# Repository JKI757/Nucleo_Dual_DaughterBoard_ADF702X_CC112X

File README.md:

## About the Project

- This project is a simple PCB for an STM32 Nucleo-64 Hat that provides an interface between the hat and an Analog Devices [ADF-702X](https://www.analog.com/en/design-center/evaluation-hardware-and-software/evaluation-boards-kits/eval-adf7021-n.html) development board and a Texas Instruments [CC112X EMK](https://www.ti.com/tool/CC1120EMK-420-470) development board.

The project includes both the Kicad schematic and PCB files, and the STM project for the Nucleo-64 L452RE.

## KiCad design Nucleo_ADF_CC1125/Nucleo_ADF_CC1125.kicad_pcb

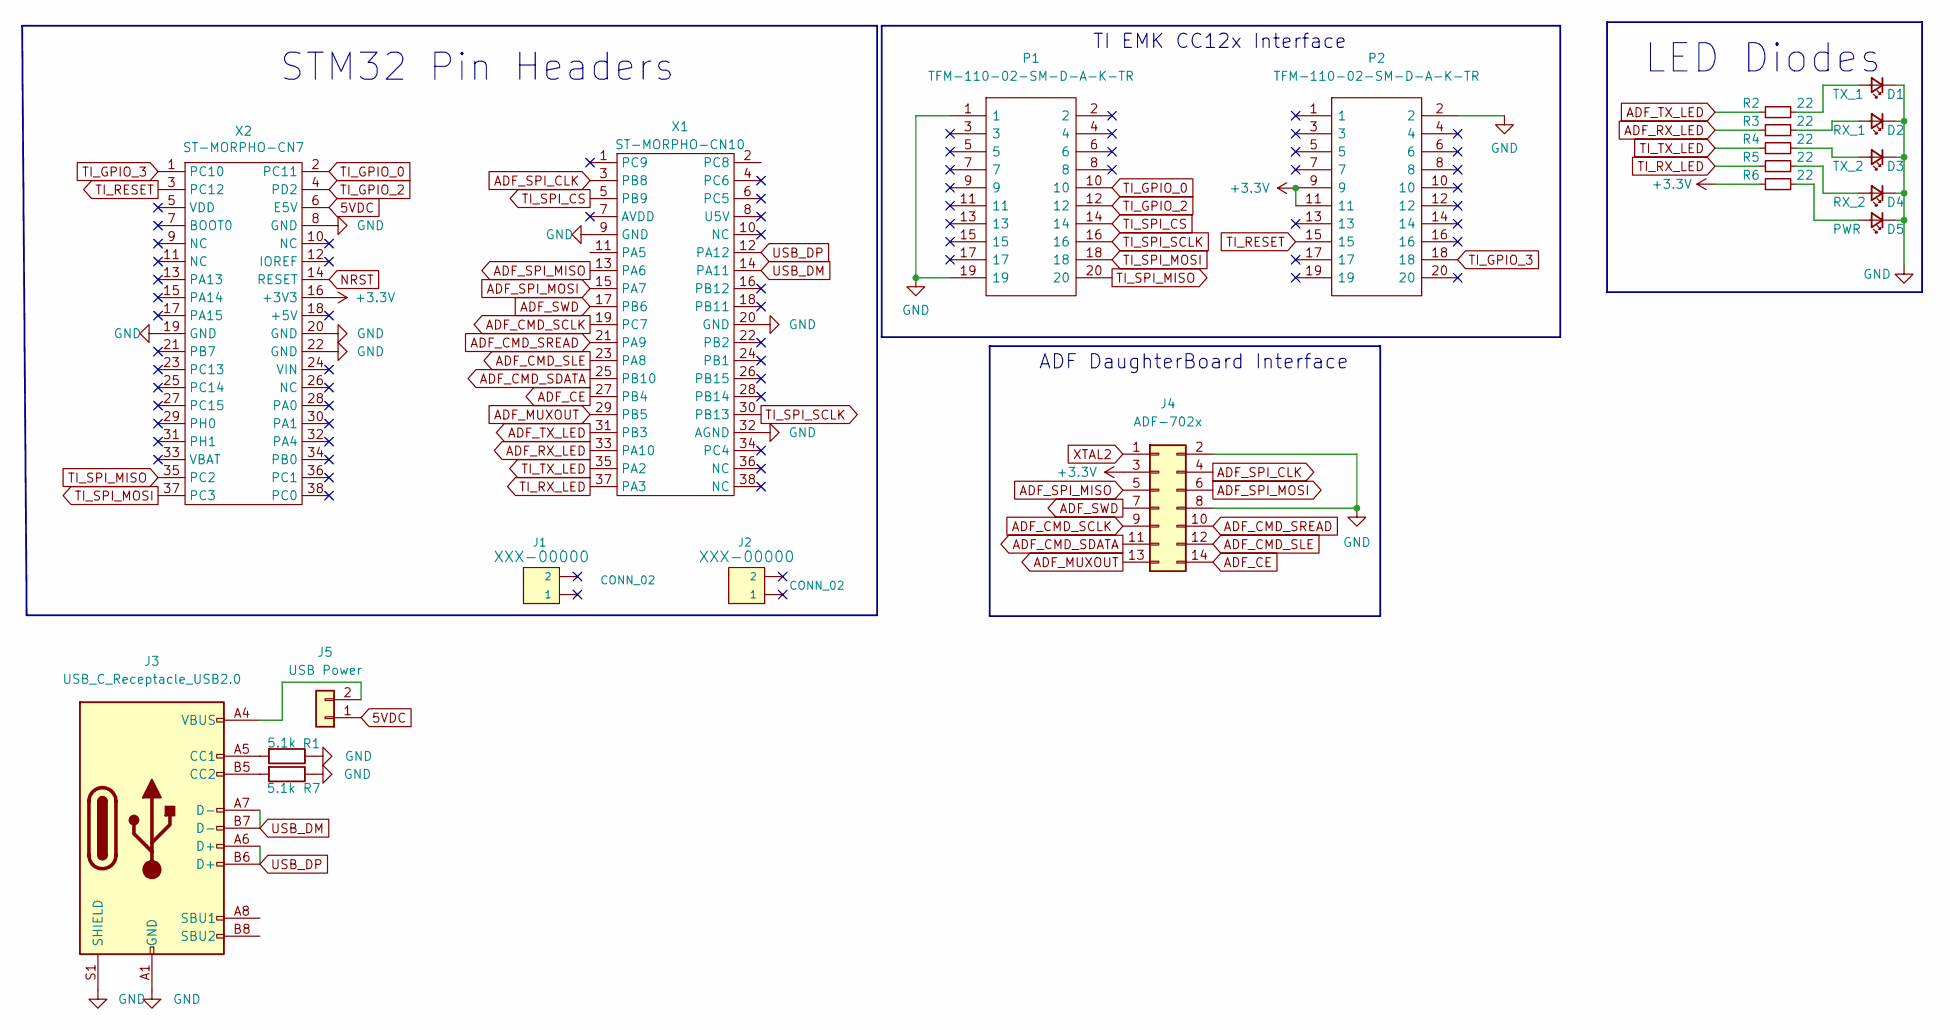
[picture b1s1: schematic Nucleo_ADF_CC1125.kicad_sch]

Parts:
D1: TX_1; LED_0402_1005Metric
D2: RX_1; LED_0402_1005Metric
D3: TX_2; LED_0402_1005Metric
D4: RX_2; LED_0402_1005Metric
D5: PWR; LED_0402_1005Metric
J1, J2: CONN_02; PinSocket_1x02_P2.54mm_Vertical
J3: USB_C_Receptacle_USB2.0; USB_C_Receptacle_JAE_DX07S016JA1R1500
J4: ADF-702x; PinHeader_2x07_P2.54mm_Vertical
J5: USB Power; PinHeader_1x02_P2.54mm_Vertical
P1, P2: TFM-110-02-SM-D-A-K-TR; TFM-110-02-XXX-D-A-Y-TR; Mouser Part Number 200-TFM11002SMDAKTR
R1, R7: 5.1k; R_0402_1005Metric
R2, R3, R4, R5, R6: 22; R_0402_1005Metric
X1: ST-MORPHO-CN10; PinSocket_2x19_P2.54mm_Vertical
X2: ST-MORPHO-CN7; PinSocket_2x19_P2.54mm_Vertical

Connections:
5VDC: J5.1, X2.6 (E5V)
+3V3: J4.3, P2.9, P2.11, R6.1, X2.16 (+3V3)
ADF_CE: J4.14, X1.27 (PB4)
ADF_CMD_SCLK: J4.9, X1.19 (PC7)
ADF_CMD_SDATA: J4.11, X1.25 (PB10)
ADF_CMD_SLE: J4.12, X1.23 (PA8)
ADF_CMD_SREAD: J4.10, X1.21 (PA9)
ADF_MUXOUT: J4.13, X1.29 (PB5)
ADF_RX_LED: R3.1, X1.33 (PA10)
ADF_SPI_CLK: J4.4, X1.3 (PB8)
ADF_SPI_MISO: J4.5, X1.13 (PA6)
ADF_SPI_MOSI: J4.6, X1.15 (PA7)
ADF_SWD: J4.7, X1.17 (PB6)
ADF_TX_LED: R2.1, X1.31 (PB3)
GND: D1.1 (K), D2.1 (K), D3.1 (K), D4.1 (K), D5.1 (K), J3.A1 (GND), J3.A12 (GND), J3.B1 (GND), J3.B12 (GND), J3.S1 (SHIELD), J4.2, J4.8, P1.1, P1.19, P2.2, R1.1, R7.1, X1.9 (GND), X1.20 (GND), X1.32 (AGND), X2.8 (GND), X2.19 (GND), X2.20 (GND), X2.22 (GND)
NRST: X2.14 (RESET)
unnamed: D1.2 (A), R2.2
unnamed: D2.2 (A), R3.2
unnamed: D3.2 (A), R4.2
unnamed: D4.2 (A), R5.2
unnamed: D5.2 (A), R6.2
unnamed: J3.A4 (VBUS), J3.A9 (VBUS), J3.B4 (VBUS), J3.B9 (VBUS), J5.2
unnamed: J3.A5 (CC1), R1.2
unnamed: J3.B5 (CC2), R7.2
TI_GPIO_0: P1.10, X2.2 (PC11)
TI_GPIO_2: P1.12, X2.4 (PD2)
TI_GPIO_3: P2.18, X2.1 (PC10)
TI_RESET: P2.15, X2.3 (PC12)
TI_RX_LED: R5.1, X1.37 (PA3)
TI_SPI_CS: P1.14, X1.5 (PB9)
TI_SPI_MISO: P1.20, X2.35 (PC2)
TI_SPI_MOSI: P1.18, X2.37 (PC3)
TI_SPI_SCLK: P1.16, X1.30 (PB13)
TI_TX_LED: R4.1, X1.35 (PA2)
USB_DM: J3.A7 (D-), J3.B7 (D-), X1.14 (PA11)
USB_DP: J3.A6 (D+), J3.B6 (D+), X1.12 (PA12)
XTAL2: J4.1

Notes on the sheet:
TI EMK CC12x Interface
STM32 Pin Headers
LED Diodes
ADF DaughterBoard Interface

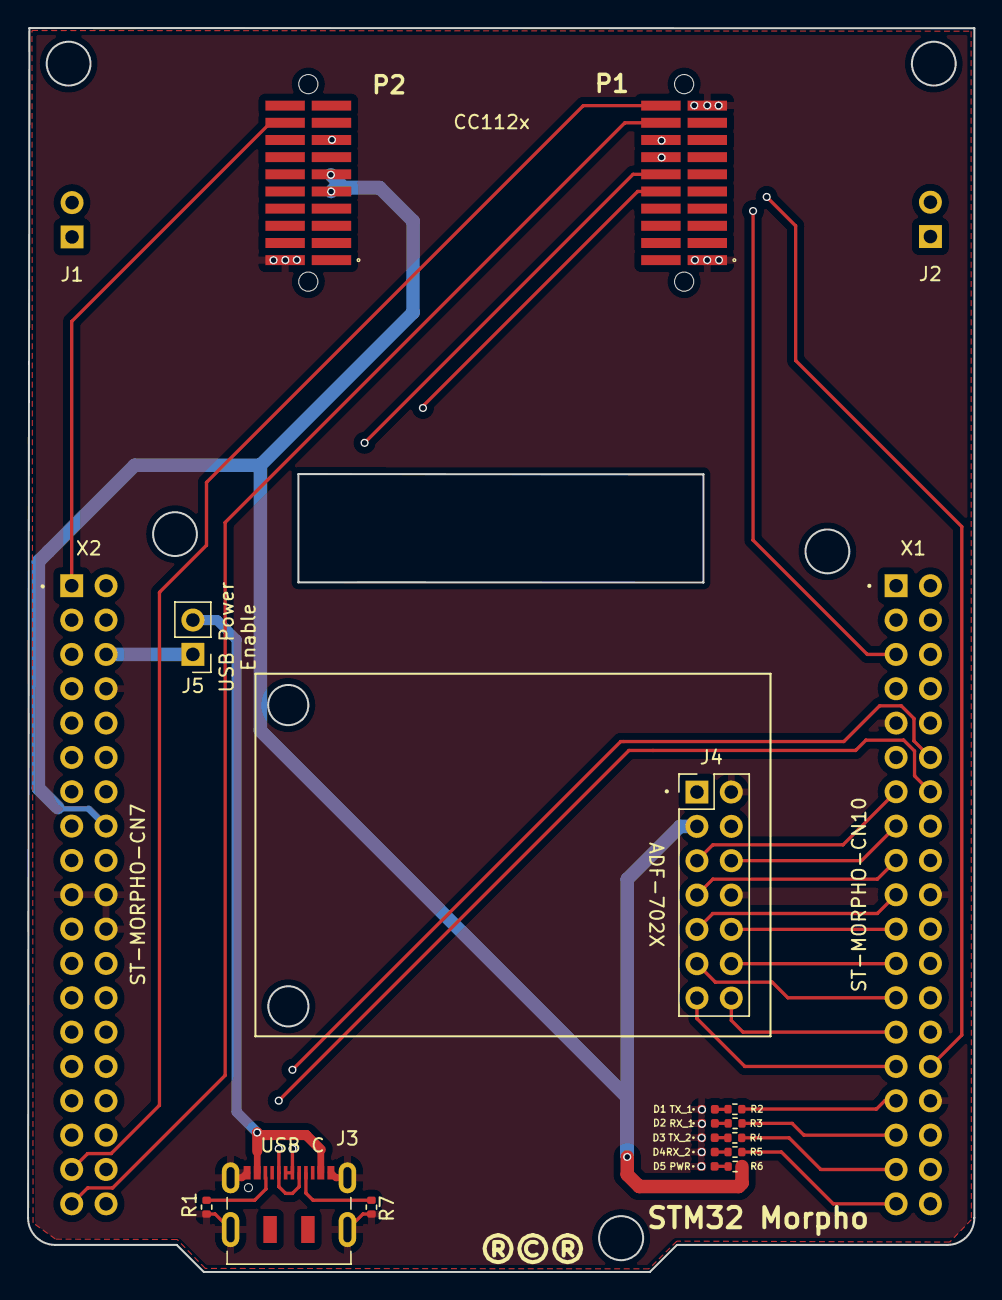
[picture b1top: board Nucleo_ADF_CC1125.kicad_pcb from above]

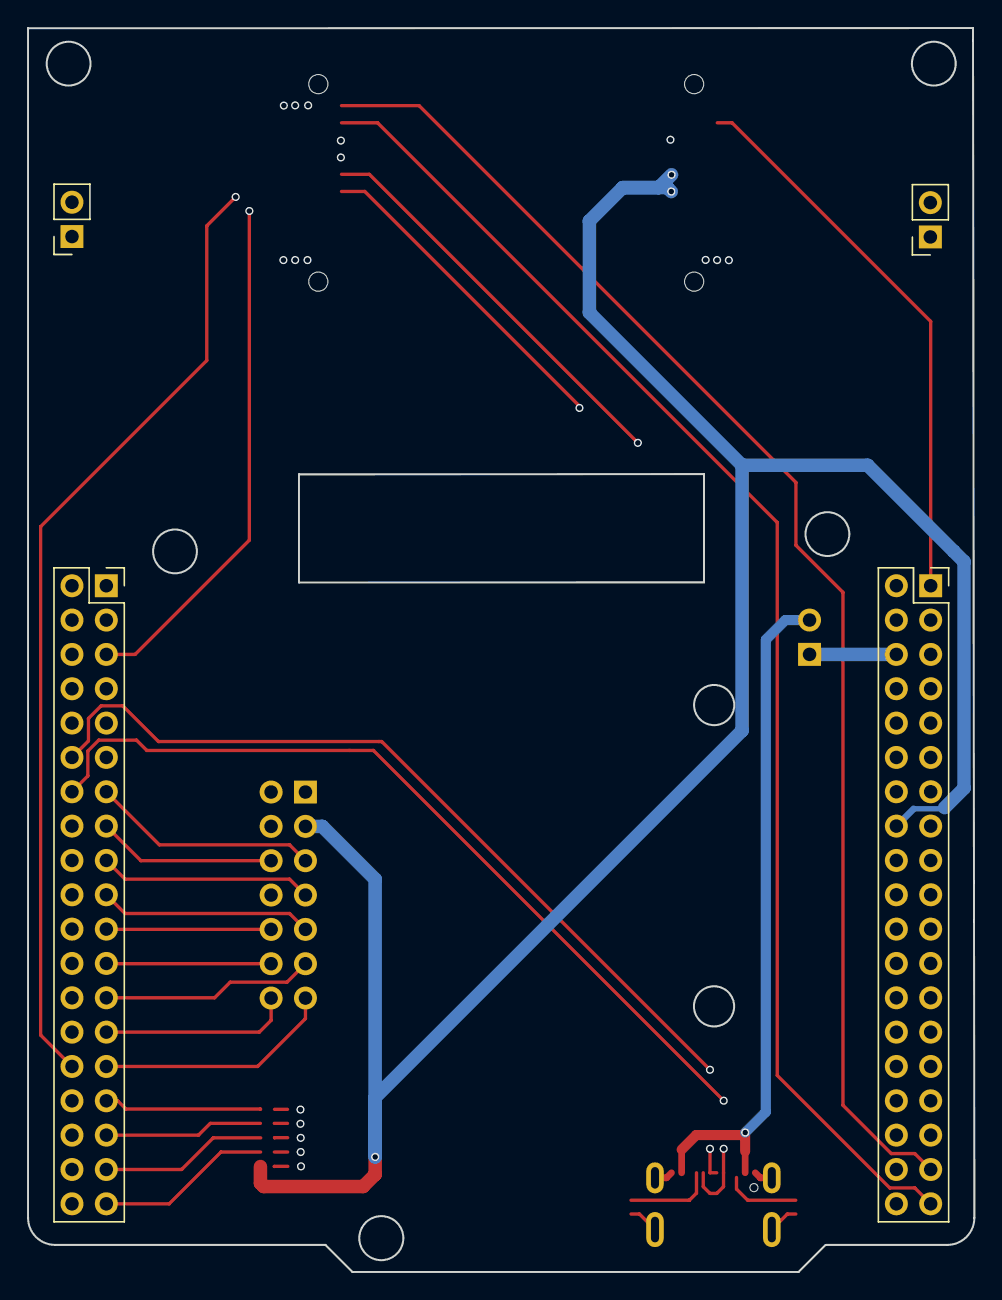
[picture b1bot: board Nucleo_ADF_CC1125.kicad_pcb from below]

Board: 4 copper layers, 70.0 x 92.0 mm, 21 parts (4 on the bottom side), 35 nets.

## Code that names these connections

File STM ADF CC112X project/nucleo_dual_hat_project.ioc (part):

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Mcu.Name=STM32L452R(C-E)Tx
Mcu.Package=LQFP64
Mcu.UserName=STM32L452RETx
PA10.GPIOParameters=GPIO_Label
PA10.GPIO_Label=ADF_RX_LED
PA10.Signal=GPIO_Output
PA11.Mode=Device
PA11.Signal=USB_DM
PA12.Mode=Device
PA12.Signal=USB_DP
PA13\ (JTMS/SWDIO).GPIOParameters=GPIO_Label
PA13\ (JTMS/SWDIO).GPIO_Label=TMS
PA13\ (JTMS/SWDIO).Mode=Serial_Wire
PA13\ (JTMS/SWDIO).Signal=SYS_JTMS-SWDIO
PA14\ (JTCK/SWCLK).GPIOParameters=GPIO_Label
PA14\ (JTCK/SWCLK).GPIO_Label=TCK
PA14\ (JTCK/SWCLK).Mode=Serial_Wire
PA14\ (JTCK/SWCLK).Signal=SYS_JTCK-SWCLK
PA2.GPIOParameters=GPIO_Label
PA2.GPIO_Label=TI_TX_LED
PA2.Signal=GPIO_Output
PA3.GPIOParameters=GPIO_Label
PA3.GPIO_Label=TI_RX_LED
PA3.Signal=GPIO_Output
PA5.GPIOParameters=GPIO_Speed,GPIO_PuPd,GPIO_Label,GPIO_ModeDefaultOutputPP
PA5.GPIO_Label=LD4 [green Led]
PA5.GPIO_ModeDefaultOutputPP=GPIO_MODE_OUTPUT_PP
PA5.GPIO_PuPd=GPIO_NOPULL
PA5.GPIO_Speed=GPIO_SPEED_FREQ_LOW
PA5.Signal=GPIO_Output
PA6.GPIOParameters=GPIO_Label
PA6.GPIO_Label=ADF_SPI_MISO
PA6.Signal=GPIO_Output
PA7.GPIOParameters=GPIO_Label
PA7.GPIO_Label=ADF_SPI_MOSI
PA7.Signal=GPIO_Input
PA8.GPIOParameters=GPIO_Label
PA8.GPIO_Label=ADF_CMD_SLE
PA8.Signal=GPIO_Output
PA9.GPIOParameters=GPIO_Label
PA9.GPIO_Label=ADF_CMD_SREAD
PA9.Signal=GPIO_Input
PB10.GPIOParameters=GPIO_Label
PB10.GPIO_Label=ADF_CMD_SDATA
PB10.Signal=GPIO_Output
PB13.Mode=Full_Duplex_Master
PB13.Signal=SPI2_SCK
PB3\ (JTDO/TRACESWO).GPIOParameters=GPIO_Label
PB3\ (JTDO/TRACESWO).GPIO_Label=ADF_TX_LED
PB3\ (JTDO/TRACESWO).Signal=GPIO_Output
PB4\ (NJTRST).GPIOParameters=GPIO_Label
PB4\ (NJTRST).GPIO_Label=ADF_CE
PB4\ (NJTRST).Signal=GPIO_Output
PB5.GPIOParameters=GPIO_Label
PB5.GPIO_Label=ADF_MUXOUT
PB5.Signal=GPIO_Input
PB6.GPIOParameters=GPIO_Label
PB6.GPIO_Label=ADF_SWD
PB6.Signal=GPXTI6
PB8.GPIOParameters=GPIO_Label
PB8.GPIO_Label=ADF_SPI_CLK
PB8.Signal=GPXTI8
PB9.Mode=NSS_Signal_Hard_Output
PB9.Signal=SPI2_NSS
PC10.GPIOParameters=GPIO_Label
PC10.GPIO_Label=TI_GPIO_3
PC10.Signal=GPXTI10
PC11.GPIOParameters=GPIO_Label
PC11.GPIO_Label=TI_GPIO_0
PC11.Signal=GPXTI11
PC12.GPIOParameters=GPIO_Label
PC12.GPIO_Label=TI_RESET
PC12.Signal=GPIO_Output
PC13.GPIOParameters=GPIO_PuPd,GPIO_Label,GPIO_ModeDefaultEXTI
PC13.GPIO_Label=B1 [Blue PushButton]
PC13.GPIO_ModeDefaultEXTI=GPIO_MODE_IT_FALLING
PC13.GPIO_PuPd=GPIO_NOPULL
PC13.Signal=GPXTI13
PC14-OSC32_IN\ (PC14).Mode=LSE-External-Oscillator
PC14-OSC32_IN\ (PC14).Signal=RCC_OSC32_IN
PC15-OSC32_OUT\ (PC15).Mode=LSE-External-Oscillator
PC15-OSC32_OUT\ (PC15).Signal=RCC_OSC32_OUT
PC2.Mode=Full_Duplex_Master
PC2.Signal=SPI2_MISO
PC3.Mode=Full_Duplex_Master
PC3.Signal=SPI2_MOSI
PC7.GPIOParameters=GPIO_Label
PC7.GPIO_Label=ADF_CMD_SCLK
PC7.Signal=GPIO_Output
PD2.GPIOParameters=GPIO_Label
PD2.GPIO_Label=TI_GPIO_2
PD2.Signal=GPXTI2
PH0-OSC_IN\ (PH0).Signal=RCC_OSC_IN
PH1-OSC_OUT\ (PH1).Signal=RCC_OSC_OUT
RCC.HSE_VALUE=8000000
RCC.SYSCLKFreq_VALUE=32000000
RCC.SYSCLKSource=RCC_SYSCLKSOURCE_PLLCLK
board=NUCLEO-L452RE
boardIOC=true

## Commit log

2022-05-14 add images
2022-05-14 add README
2022-05-14 fix README
2022-05-14 fix images
2022-05-14 add to readme
